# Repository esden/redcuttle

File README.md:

Welcome to RedCuttle.

This project is the hardware and software for a JTAG/SWD/UART port multiplexer
and switcher.

This hardware allows the control of multiple debuggers and targets to be
connected to one another for development and testing purposes. The original
motivation for this is the Hardware In The Loop testing of the Black Magic
Debug firmware on Black Magic Probe hardware.

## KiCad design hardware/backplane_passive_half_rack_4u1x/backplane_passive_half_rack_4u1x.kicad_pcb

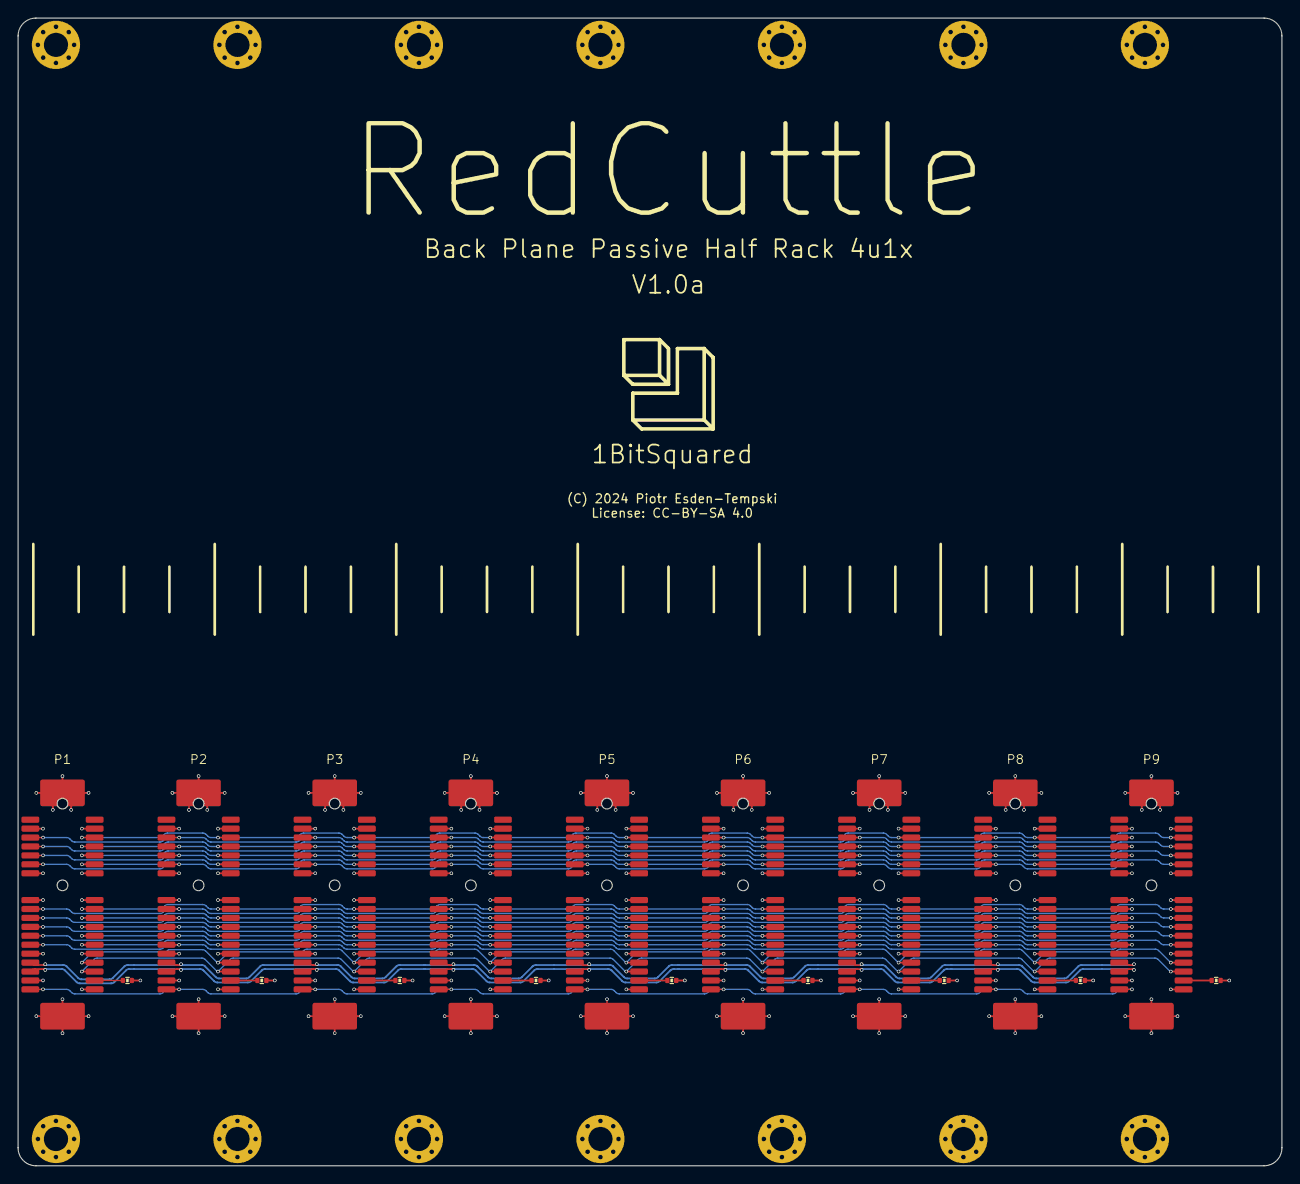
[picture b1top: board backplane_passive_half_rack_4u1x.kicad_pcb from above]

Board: 4 copper layers, 141.5 x 128.5 mm, 18 parts (0 on the bottom side), 34 nets.

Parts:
P1, P2, P3, P4, P5, P6, P7, P8, P9: XDMP-052-0360
R1: 487; R_0402
R2: 845; R_0402
R4: 1k24; R_0402
R5: 1k65; R_0402
R6: 2k1; R_0402
R7: 2k55; R_0402
R8: 3k09; R_0402
R9: 3k65; R_0402
R10: 4k22; R_0402

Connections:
+5V: P1.B1 (5V), P2.B1 (5V), P3.B1 (5V), P4.B1 (5V), P5.B1 (5V), P6.B1 (5V), P7.B1 (5V), P8.B1 (5V), P9.B1 (5V)
/D_N: P1.A4 (D_N), P2.A4 (D_N), P3.A4 (D_N), P4.A4 (D_N), P5.A4 (D_N), P6.A4 (D_N), P7.A4 (D_N), P8.A4 (D_N), P9.A4 (D_N)
/D_P: P1.A3 (D_P), P2.A3 (D_P), P3.A3 (D_P), P4.A3 (D_P), P5.A3 (D_P), P6.A3 (D_P), P7.A3 (D_P), P8.A3 (D_P), P9.A3 (D_P)
/JTCK: P1.B7 (JTCK), P2.B7 (JTCK), P3.B7 (JTCK), P4.B7 (JTCK), P5.B7 (JTCK), P6.B7 (JTCK), P7.B7 (JTCK), P8.B7 (JTCK), P9.B7 (JTCK)
/JTDI: P1.B9 (JTDI), P2.B9 (JTDI), P3.B9 (JTDI), P4.B9 (JTDI), P5.B9 (JTDI), P6.B9 (JTDI), P7.B9 (JTDI), P8.B9 (JTDI), P9.B9 (JTDI)
/JTDO: P1.B8 (JTDO), P2.B8 (JTDO), P3.B8 (JTDO), P4.B8 (JTDO), P5.B8 (JTDO), P6.B8 (JTDO), P7.B8 (JTDO), P8.B8 (JTDO), P9.B8 (JTDO)
/JTMS: P1.B6 (JTMS), P2.B6 (JTMS), P3.B6 (JTMS), P4.B6 (JTMS), P5.B6 (JTMS), P6.B6 (JTMS), P7.B6 (JTMS), P8.B6 (JTMS), P9.B6 (JTMS)
/MGMT_SCL: P1.B4 (MGMT_SCL), P2.B4 (MGMT_SCL), P3.B4 (MGMT_SCL), P4.B4 (MGMT_SCL), P5.B4 (MGMT_SCL), P6.B4 (MGMT_SCL), P7.B4 (MGMT_SCL), P8.B4 (MGMT_SCL), P9.B4 (MGMT_SCL)
/MGMT_SDA: P1.B3 (MGMT_SDA), P2.B3 (MGMT_SDA), P3.B3 (MGMT_SDA), P4.B3 (MGMT_SDA), P5.B3 (MGMT_SDA), P6.B3 (MGMT_SDA), P7.B3 (MGMT_SDA), P8.B3 (MGMT_SDA), P9.B3 (MGMT_SDA)
/NRST: P1.B10 (NRST), P2.B10 (NRST), P3.B10 (NRST), P4.B10 (NRST), P5.B10 (NRST), P6.B10 (NRST), P7.B10 (NRST), P8.B10 (NRST), P9.B10 (NRST)
/SLOT1/GPIO0: P1.B13 (GPIO0), P2.B13 (GPIO0), P3.B13 (GPIO0), P4.B13 (GPIO0), P5.B13 (GPIO0), P6.B13 (GPIO0), P7.B13 (GPIO0), P8.B13 (GPIO0), P9.B13 (GPIO0)
/SLOT1/GPIO1: P1.B14 (GPIO1), P2.B14 (GPIO1), P3.B14 (GPIO1), P4.B14 (GPIO1), P5.B14 (GPIO1), P6.B14 (GPIO1), P7.B14 (GPIO1), P8.B14 (GPIO1), P9.B14 (GPIO1)
/SLOT1/GPIO2: P1.B15 (GPIO2), P2.B15 (GPIO2), P3.B15 (GPIO2), P4.B15 (GPIO2), P5.B15 (GPIO2), P6.B15 (GPIO2), P7.B15 (GPIO2), P8.B15 (GPIO2), P9.B15 (GPIO2)
/SLOT1/GPIO3: P1.B16 (GPIO3), P2.B16 (GPIO3), P3.B16 (GPIO3), P4.B16 (GPIO3), P5.B16 (GPIO3), P6.B16 (GPIO3), P7.B16 (GPIO3), P8.B16 (GPIO3), P9.B16 (GPIO3)
/SLOT1/GPIO4: P1.A13 (GPIO4), P2.A13 (GPIO4), P3.A13 (GPIO4), P4.A13 (GPIO4), P5.A13 (GPIO4), P6.A13 (GPIO4), P7.A13 (GPIO4), P8.A13 (GPIO4), P9.A13 (GPIO4)
/SLOT1/GPIO5: P1.A14 (GPIO5), P2.A14 (GPIO5), P3.A14 (GPIO5), P4.A14 (GPIO5), P5.A14 (GPIO5), P6.A14 (GPIO5), P7.A14 (GPIO5), P8.A14 (GPIO5), P9.A14 (GPIO5)
/SLOT1/GPIO6: P1.A15 (GPIO6), P2.A15 (GPIO6), P3.A15 (GPIO6), P4.A15 (GPIO6), P5.A15 (GPIO6), P6.A15 (GPIO6), P7.A15 (GPIO6), P8.A15 (GPIO6), P9.A15 (GPIO6)
/SLOT1/GPIO7: P1.A16 (GPIO7), P2.A16 (GPIO7), P3.A16 (GPIO7), P4.A16 (GPIO7), P5.A16 (GPIO7), P6.A16 (GPIO7), P7.A16 (GPIO7), P8.A16 (GPIO7), P9.A16 (GPIO7)
/SLOT1/TRACE.CLK: P1.A6 (TRACECLK), P2.A6 (TRACECLK), P3.A6 (TRACECLK), P4.A6 (TRACECLK), P5.A6 (TRACECLK), P6.A6 (TRACECLK), P7.A6 (TRACECLK), P8.A6 (TRACECLK), P9.A6 (TRACECLK)
/SLOT1/TRACE.D0: P1.A7 (TRACED0), P2.A7 (TRACED0), P3.A7 (TRACED0), P4.A7 (TRACED0), P5.A7 (TRACED0), P6.A7 (TRACED0), P7.A7 (TRACED0), P8.A7 (TRACED0), P9.A7 (TRACED0)
/SLOT1/TRACE.D1: P1.A8 (TRACED1), P2.A8 (TRACED1), P3.A8 (TRACED1), P4.A8 (TRACED1), P5.A8 (TRACED1), P6.A8 (TRACED1), P7.A8 (TRACED1), P8.A8 (TRACED1), P9.A8 (TRACED1)
/SLOT1/TRACE.D2: P1.A9 (TRACED2), P2.A9 (TRACED2), P3.A9 (TRACED2), P4.A9 (TRACED2), P5.A9 (TRACED2), P6.A9 (TRACED2), P7.A9 (TRACED2), P8.A9 (TRACED2), P9.A9 (TRACED2)
/SLOT1/TRACE.D3: P1.A10 (TRACED3), P2.A10 (TRACED3), P3.A10 (TRACED3), P4.A10 (TRACED3), P5.A10 (TRACED3), P6.A10 (TRACED3), P7.A10 (TRACED3), P8.A10 (TRACED3), P9.A10 (TRACED3)
/VTREF: P1.A1 (VTREF), P2.A1 (VTREF), P3.A1 (VTREF), P4.A1 (VTREF), P5.A1 (VTREF), P6.A1 (VTREF), P7.A1 (VTREF), P8.A1 (VTREF), P9.A1 (VTREF)
GND: P1.A2 (GND), P1.A5 (GND), P1.A11 (GND), P1.A12 (GND), P1.A17 (GND), P1.B5 (GND), P1.B11 (GND), P1.B12 (GND), P1.B17 (GND), P1.MP, P2.A2 (GND), P2.A5 (GND), P2.A11 (GND), P2.A12 (GND), P2.A17 (GND), P2.B5 (GND), P2.B11 (GND), P2.B12 (GND), P2.B17 (GND), P2.MP, P3.A2 (GND), P3.A5 (GND), P3.A11 (GND), P3.A12 (GND), P3.A17 (GND), P3.B5 (GND), P3.B11 (GND), P3.B12 (GND), P3.B17 (GND), P3.MP, P4.A2 (GND), P4.A5 (GND), P4.A11 (GND), P4.A12 (GND), P4.A17 (GND), P4.B5 (GND), P4.B11 (GND), P4.B12 (GND), P4.B17 (GND), P4.MP, P5.A2 (GND), P5.A5 (GND), P5.A11 (GND), P5.A12 (GND), P5.A17 (GND), P5.B5 (GND), P5.B11 (GND), P5.B12 (GND), P5.B17 (GND), P5.MP, P6.A2 (GND), P6.A5 (GND), P6.A11 (GND), P6.A12 (GND), P6.A17 (GND), P6.B5 (GND), P6.B11 (GND), P6.B12 (GND), P6.B17 (GND), P6.MP, P7.A2 (GND), P7.A5 (GND), P7.A11 (GND), P7.A12 (GND), P7.A17 (GND), P7.B5 (GND), P7.B11 (GND), P7.B12 (GND), P7.B17 (GND), P7.MP, P8.A2 (GND), P8.A5 (GND), P8.A11 (GND), P8.A12 (GND), P8.A17 (GND), P8.B5 (GND), P8.B11 (GND), P8.B12 (GND), P8.B17 (GND), P8.MP, P9.A2 (GND), P9.A5 (GND), P9.A11 (GND), P9.A12 (GND), P9.A17 (GND), P9.B5 (GND), P9.B11 (GND), P9.B12 (GND), P9.B17 (GND), P9.MP, R1.2, R2.2, R4.2, R5.2, R6.2, R7.2, R8.2, R9.2, R10.2
unnamed: P1.B2 (ADDR), R1.1
unnamed: P2.B2 (ADDR), R2.1
unnamed: P3.B2 (ADDR), R4.1
unnamed: P4.B2 (ADDR), R5.1
unnamed: P5.B2 (ADDR), R6.1
unnamed: P6.B2 (ADDR), R7.1
unnamed: P7.B2 (ADDR), R8.1
unnamed: P8.B2 (ADDR), R9.1
unnamed: P9.B2 (ADDR), R10.1

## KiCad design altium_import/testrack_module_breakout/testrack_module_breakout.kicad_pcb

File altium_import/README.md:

These boards were designed by @zyp. They are the reference and the goal for RedCuttle is to be compatible with @zyp design.

Thank you @zyp for letting me convert your design and include it here. :)

All files in this directory are licensed under CC-BY-SA 4.0

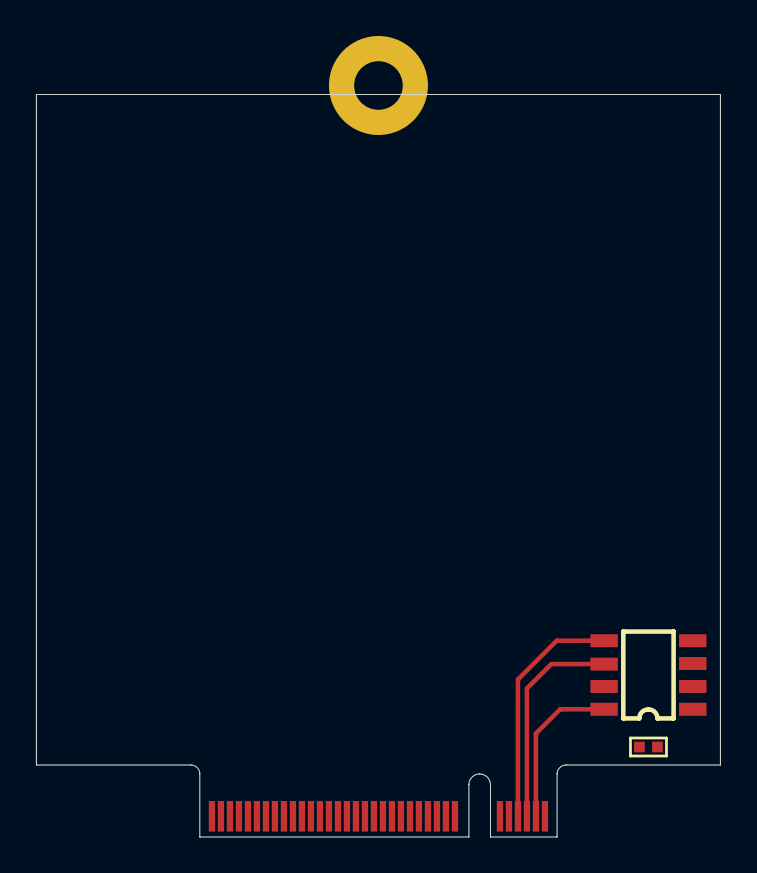
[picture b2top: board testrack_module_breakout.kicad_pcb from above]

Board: 2 copper layers, 38.0 x 41.2 mm, 3 parts (0 on the bottom side), 5 nets.

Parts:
C1: 100nF; 0402
P1: M.2_B; M.2_B_EDGE
U1: 24Cxx; SO8

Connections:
GND: C1.1, P1.1, P1.2, P1.10, P1.11, P1.20, P1.21, P1.32, P1.33, P1.38, P1.39, P1.56, P1.57, P1.74, P1.75, U1.4
MGMT_SCL: P1.5, U1.6
MGMT_SDA: P1.7, U1.5
VIN: P1.4, P1.6
VMGMT: C1.2, P1.3, U1.8

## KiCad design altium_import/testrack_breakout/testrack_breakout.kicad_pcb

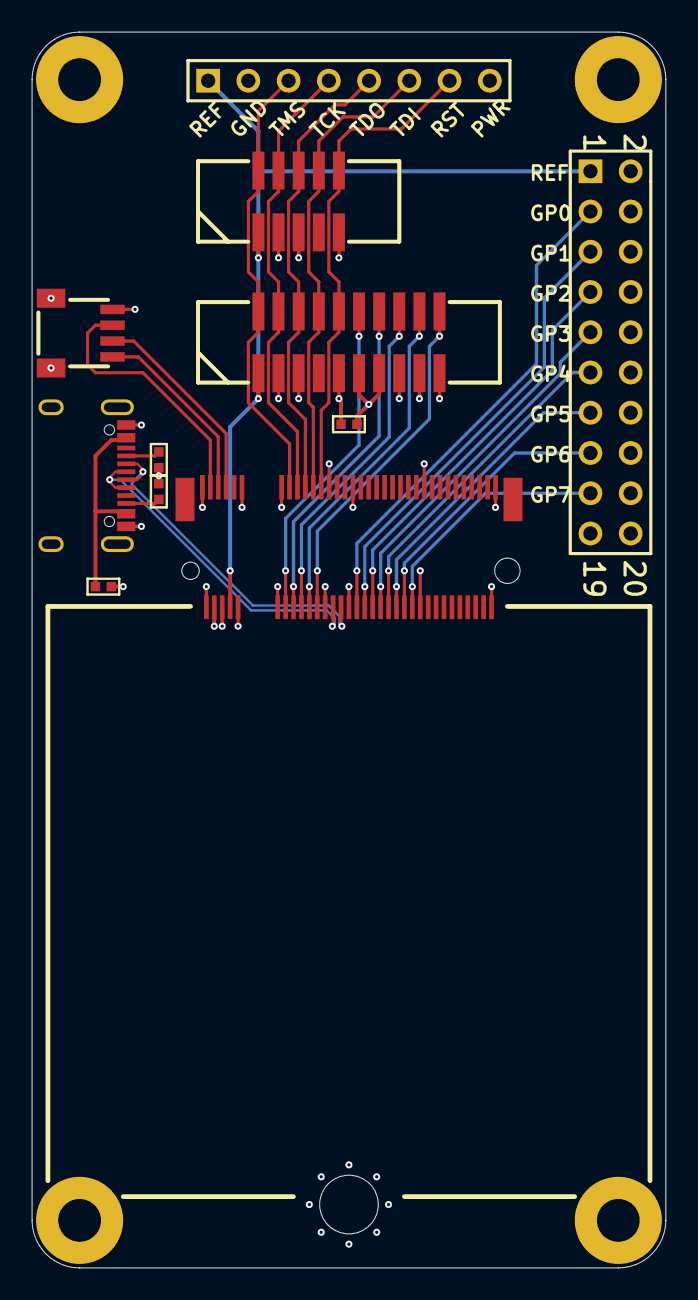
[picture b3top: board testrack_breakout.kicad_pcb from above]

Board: 4 copper layers, 40.0 x 78.0 mm, 12 parts (0 on the bottom side), 29 nets.

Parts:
C1: 100nF; 0402
MH1: Mounting_Hole; WA-SMSI_M2.5
P1: M.2_B
P2: SWD-TRACE-FTSH110; FTSH110
P3: SWD-FTSH105; FTSH105
P4: USBC; U262-161N-4BVC11
P5: Header 10X2; HDR2X10
P6: SH4_I2C; SM04B
P7: Header 8; HDR1X8
R2, R3: 5.1k; 0402
R4: NP; 0402

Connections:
D_N: P1.36, P4.A7, P4.B7
D_P: P1.34, P4.A6, P4.B6
GND: C1.1, MH1.1, P1.1, P1.2, P1.10, P1.11, P1.20, P1.21, P1.32, P1.33, P1.38, P1.39, P1.56, P1.57, P1.74, P1.75, P2.3, P2.5, P2.9, P2.15, P2.17, P2.19, P3.3, P3.5, P3.9, P4.A1, P4.A12, P4.B1, P4.B12, P4.SH, P5.4, P5.6, P5.8, P5.10, P5.12, P5.14, P5.16, P5.18, P6.1, P6.SH, P7.2, R2.1, R3.1
GPIO0: P1.40, P5.3
GPIO1: P1.42, P5.5
GPIO2: P1.44, P5.7
GPIO3: P1.46, P5.9
GPIO4: P1.48, P5.11
GPIO5: P1.50, P5.13
GPIO6: P1.52, P5.15
GPIO7: P1.54, P5.17
JTCK: P1.25, P2.4, P3.4, P7.4
JTDI: P1.29, P2.8, P3.8, P7.6
JTDO: P1.27, P2.6, P3.6, P7.5
JTMS: P1.23, P2.2, P3.2, P7.3
NRST: P1.31, P2.10, P3.10, P7.7
NetP4_A4: P4.A4, P4.A9, P4.B4, P4.B9, R4.2
NetP4_A5: P4.A5, R2.2
NetP4_B5: P4.B5, R3.2
SCL: P1.5, P6.4
SDA: P1.7, P6.3
TRACECLK: P1.22, P2.12
TRACED0: P1.24, P2.14
TRACED1: P1.26, P2.16
TRACED2: P1.28, P2.18
TRACED3: P1.30, P2.20
V3.3: P1.3, P6.2
VTPWR: C1.2, P1.4, P1.6, P2.11, P2.13, P7.8, R4.1
VTREF: P1.8, P2.1, P3.1, P5.1, P7.1

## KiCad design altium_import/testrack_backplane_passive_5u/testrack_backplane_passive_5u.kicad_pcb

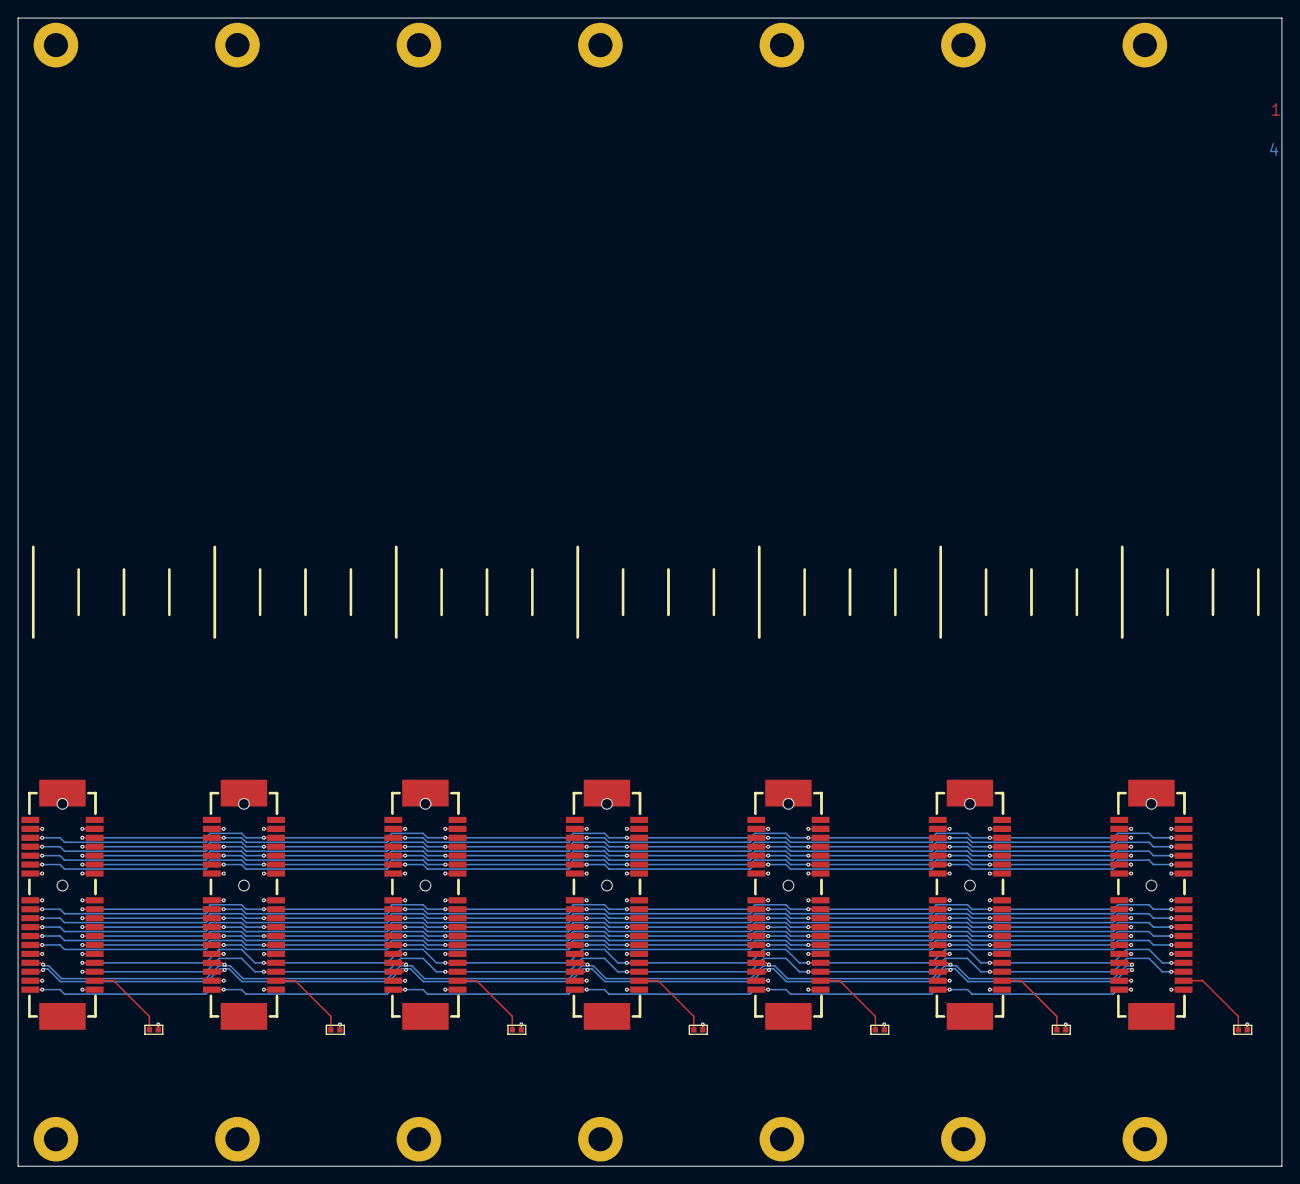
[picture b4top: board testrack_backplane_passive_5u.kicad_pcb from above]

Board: 4 copper layers, 141.5 x 128.6 mm, 14 parts (0 on the bottom side), 32 nets.

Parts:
P1_SLOT1, P1_SLOT2, P1_SLOT3, P1_SLOT4, P1_SLOT5, P1_SLOT6, P1_SLOT7: PCIE_X1; PCIE_X1_SMT
R1_SLOT1: 487; 0402
R1_SLOT2: 845; 0402
R1_SLOT3: 1.24k; 0402
R1_SLOT4: 1.65k; 0402
R1_SLOT5: 2.10k; 0402
R1_SLOT6: 2.55k; 0402
R1_SLOT7: 3.09k; 0402

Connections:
ADDR_SLOT1: P1_SLOT1.B2, R1_SLOT1.2
ADDR_SLOT2: P1_SLOT2.B2, R1_SLOT2.2
ADDR_SLOT3: P1_SLOT3.B2, R1_SLOT3.2
ADDR_SLOT4: P1_SLOT4.B2, R1_SLOT4.2
ADDR_SLOT5: P1_SLOT5.B2, R1_SLOT5.2
ADDR_SLOT6: P1_SLOT6.B2, R1_SLOT6.2
ADDR_SLOT7: P1_SLOT7.B2, R1_SLOT7.2
GND: P1_SLOT1.A2, P1_SLOT1.A5, P1_SLOT1.A11, P1_SLOT1.A12, P1_SLOT1.A17, P1_SLOT1.B5, P1_SLOT1.B11, P1_SLOT1.B12, P1_SLOT1.B17, P1_SLOT2.A2, P1_SLOT2.A5, P1_SLOT2.A11, P1_SLOT2.A12, P1_SLOT2.A17, P1_SLOT2.B5, P1_SLOT2.B11, P1_SLOT2.B12, P1_SLOT2.B17, P1_SLOT3.A2, P1_SLOT3.A5, P1_SLOT3.A11, P1_SLOT3.A12, P1_SLOT3.A17, P1_SLOT3.B5, P1_SLOT3.B11, P1_SLOT3.B12, P1_SLOT3.B17, P1_SLOT4.A2, P1_SLOT4.A5, P1_SLOT4.A11, P1_SLOT4.A12, P1_SLOT4.A17, P1_SLOT4.B5, P1_SLOT4.B11, P1_SLOT4.B12, P1_SLOT4.B17, P1_SLOT5.A2, P1_SLOT5.A5, P1_SLOT5.A11, P1_SLOT5.A12, P1_SLOT5.A17, P1_SLOT5.B5, P1_SLOT5.B11, P1_SLOT5.B12, P1_SLOT5.B17, P1_SLOT6.A2, P1_SLOT6.A5, P1_SLOT6.A11, P1_SLOT6.A12, P1_SLOT6.A17, P1_SLOT6.B5, P1_SLOT6.B11, P1_SLOT6.B12, P1_SLOT6.B17, P1_SLOT7.A2, P1_SLOT7.A5, P1_SLOT7.A11, P1_SLOT7.A12, P1_SLOT7.A17, P1_SLOT7.B5, P1_SLOT7.B11, P1_SLOT7.B12, P1_SLOT7.B17, R1_SLOT1.1, R1_SLOT2.1, R1_SLOT3.1, R1_SLOT4.1, R1_SLOT5.1, R1_SLOT6.1, R1_SLOT7.1
GPIO0: P1_SLOT1.B13, P1_SLOT2.B13, P1_SLOT3.B13, P1_SLOT4.B13, P1_SLOT5.B13, P1_SLOT6.B13, P1_SLOT7.B13
GPIO1: P1_SLOT1.B14, P1_SLOT2.B14, P1_SLOT3.B14, P1_SLOT4.B14, P1_SLOT5.B14, P1_SLOT6.B14, P1_SLOT7.B14
GPIO2: P1_SLOT1.B15, P1_SLOT2.B15, P1_SLOT3.B15, P1_SLOT4.B15, P1_SLOT5.B15, P1_SLOT6.B15, P1_SLOT7.B15
GPIO3: P1_SLOT1.B16, P1_SLOT2.B16, P1_SLOT3.B16, P1_SLOT4.B16, P1_SLOT5.B16, P1_SLOT6.B16, P1_SLOT7.B16
GPIO4: P1_SLOT1.A13, P1_SLOT2.A13, P1_SLOT3.A13, P1_SLOT4.A13, P1_SLOT5.A13, P1_SLOT6.A13, P1_SLOT7.A13
GPIO5: P1_SLOT1.A14, P1_SLOT2.A14, P1_SLOT3.A14, P1_SLOT4.A14, P1_SLOT5.A14, P1_SLOT6.A14, P1_SLOT7.A14
GPIO6: P1_SLOT1.A15, P1_SLOT2.A15, P1_SLOT3.A15, P1_SLOT4.A15, P1_SLOT5.A15, P1_SLOT6.A15, P1_SLOT7.A15
GPIO7: P1_SLOT1.A16, P1_SLOT2.A16, P1_SLOT3.A16, P1_SLOT4.A16, P1_SLOT5.A16, P1_SLOT6.A16, P1_SLOT7.A16
JTCK: P1_SLOT1.B7, P1_SLOT2.B7, P1_SLOT3.B7, P1_SLOT4.B7, P1_SLOT5.B7, P1_SLOT6.B7, P1_SLOT7.B7
JTDI: P1_SLOT1.B9, P1_SLOT2.B9, P1_SLOT3.B9, P1_SLOT4.B9, P1_SLOT5.B9, P1_SLOT6.B9, P1_SLOT7.B9
JTDO: P1_SLOT1.B8, P1_SLOT2.B8, P1_SLOT3.B8, P1_SLOT4.B8, P1_SLOT5.B8, P1_SLOT6.B8, P1_SLOT7.B8
JTMS: P1_SLOT1.B6, P1_SLOT2.B6, P1_SLOT3.B6, P1_SLOT4.B6, P1_SLOT5.B6, P1_SLOT6.B6, P1_SLOT7.B6
MGMT_SCL: P1_SLOT1.B4, P1_SLOT2.B4, P1_SLOT3.B4, P1_SLOT4.B4, P1_SLOT5.B4, P1_SLOT6.B4, P1_SLOT7.B4
MGMT_SDA: P1_SLOT1.B3, P1_SLOT2.B3, P1_SLOT3.B3, P1_SLOT4.B3, P1_SLOT5.B3, P1_SLOT6.B3, P1_SLOT7.B3
NRST: P1_SLOT1.B10, P1_SLOT2.B10, P1_SLOT3.B10, P1_SLOT4.B10, P1_SLOT5.B10, P1_SLOT6.B10, P1_SLOT7.B10
TRACECLK: P1_SLOT1.A6, P1_SLOT2.A6, P1_SLOT3.A6, P1_SLOT4.A6, P1_SLOT5.A6, P1_SLOT6.A6, P1_SLOT7.A6
TRACED0: P1_SLOT1.A7, P1_SLOT2.A7, P1_SLOT3.A7, P1_SLOT4.A7, P1_SLOT5.A7, P1_SLOT6.A7, P1_SLOT7.A7
TRACED1: P1_SLOT1.A8, P1_SLOT2.A8, P1_SLOT3.A8, P1_SLOT4.A8, P1_SLOT5.A8, P1_SLOT6.A8, P1_SLOT7.A8
TRACED2: P1_SLOT1.A9, P1_SLOT2.A9, P1_SLOT3.A9, P1_SLOT4.A9, P1_SLOT5.A9, P1_SLOT6.A9, P1_SLOT7.A9
TRACED3: P1_SLOT1.A10, P1_SLOT2.A10, P1_SLOT3.A10, P1_SLOT4.A10, P1_SLOT5.A10, P1_SLOT6.A10, P1_SLOT7.A10
USB_D_N: P1_SLOT1.A4, P1_SLOT2.A4, P1_SLOT3.A4, P1_SLOT4.A4, P1_SLOT5.A4, P1_SLOT6.A4, P1_SLOT7.A4
USB_D_P: P1_SLOT1.A3, P1_SLOT2.A3, P1_SLOT3.A3, P1_SLOT4.A3, P1_SLOT5.A3, P1_SLOT6.A3, P1_SLOT7.A3
V5: P1_SLOT1.B1, P1_SLOT2.B1, P1_SLOT3.B1, P1_SLOT4.B1, P1_SLOT5.B1, P1_SLOT6.B1, P1_SLOT7.B1
VTREF: P1_SLOT1.A1, P1_SLOT2.A1, P1_SLOT3.A1, P1_SLOT4.A1, P1_SLOT5.A1, P1_SLOT6.A1, P1_SLOT7.A1

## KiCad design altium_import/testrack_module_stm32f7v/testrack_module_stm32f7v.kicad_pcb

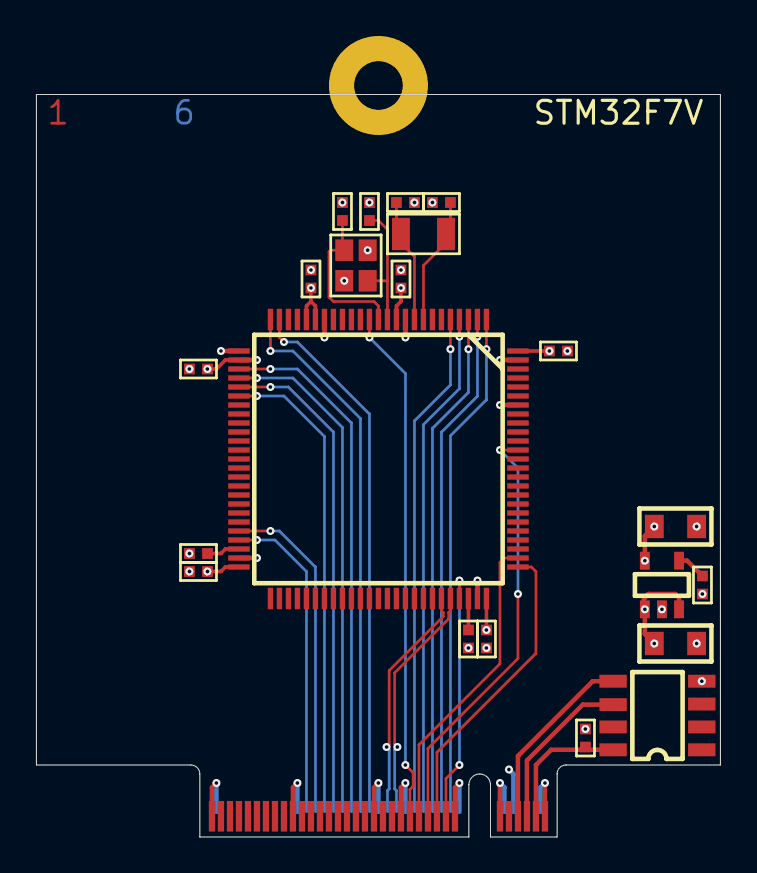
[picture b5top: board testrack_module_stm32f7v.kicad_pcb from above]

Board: 6 copper layers, 38.0 x 41.2 mm, 22 parts (0 on the bottom side), 33 nets.

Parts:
C1, C15: 100nF; 0402
C2, C3: 2.2u; 0402
C4, C5, C6, C10, C11, C12: 100n; 0402
C8, C9: 10p; 0402
C13, C14: 22uF; 0805
C16, C17: 22p; 0402
P1: M.2_B; M.2_B_EDGE
U1: 24Cxx; SO8
U2: STM32F730V; QFP100
U3: RT9193-33; SOT23-5
Y1: 12MHz; XTAL-2520-4SMD
Y2: 32.768kHz; XTAL-3215

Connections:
D_N: P1.36, U2.70
D_P: P1.34, U2.71
GND: C1.1, C2.1, C3.1, C4.1, C5.1, C6.1, C8.2, C9.2, C10.1, C11.1, C12.1, C13.1, C14.1, C15.1, C16.1, C17.1, P1.1, P1.2, P1.10, P1.11, P1.20, P1.21, P1.32, P1.33, P1.38, P1.39, P1.56, P1.57, P1.74, P1.75, U1.4, U2.10, U2.19, U2.26, U2.49, U2.74, U2.94, U2.99, U3.2, Y1.2, Y1.4
GPIO0: P1.40, U2.24
GPIO1: P1.42, U2.25
GPIO2: P1.44, U2.28
GPIO3: P1.46, U2.29
GPIO4: P1.48, U2.30
GPIO5: P1.50, U2.31
GPIO6: P1.52, U2.46
GPIO7: P1.54, U2.47
JTCK: P1.25, U2.76
JTDI: P1.29, U2.77
JTDO: P1.27, U2.89
JTMS: P1.23, U2.72
MGMT_SCL: P1.5, U1.6
MGMT_SDA: P1.7, U1.5
NRST: P1.31, U2.14
NetC2_2: C2.2, U2.73
NetC3_2: C3.2, U2.48
NetC8_1: C8.1, U2.12, Y1.1
NetC9_1: C9.1, U2.13, Y1.3
NetC15_2: C15.2, U3.4
NetC16_2: C16.2, U2.9, Y2.1
NetC17_2: C17.2, U2.8, Y2.2
TRACECLK: P1.22, U2.1
TRACED0: P1.24, U2.2
TRACED1: P1.26, U2.3
TRACED2: P1.28, U2.4
TRACED3: P1.30, U2.5
V3.3: C4.2, C5.2, C6.2, C10.2, C11.2, C12.2, C14.2, P1.8, U2.11, U2.20, U2.21, U2.27, U2.50, U2.75, U2.100, U3.5
VIN: C13.2, P1.4, P1.6, U3.1, U3.3
VMGMT: C1.2, P1.3, U1.8

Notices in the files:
hardware/backplane_passive_half_rack_4u1x/backplane_passive_half_rack_4u1x.kicad_pcb:
(C) 2024 1BitSquared
(C) 2024 Piotr Esden-Tempski
License: CC-BY-SA 4.0
